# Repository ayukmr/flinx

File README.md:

# flinx

BL654-based low-profile 40% keyboard.

The board uses Kailh Choc V2 switches, and purposely doesn't include any stabilizers.
The PCB fits directly inside the case and is mounted with four screws.
A USB-C port on the side is used for charging, and a switch turns the board on/off.
Once turned on, the keyboard pairs over Bluetooth to send keystrokes.

This is intended as a small board mostly for travel, and as a low-profile version of the Monokei Neko.

## Schematic

## PCB

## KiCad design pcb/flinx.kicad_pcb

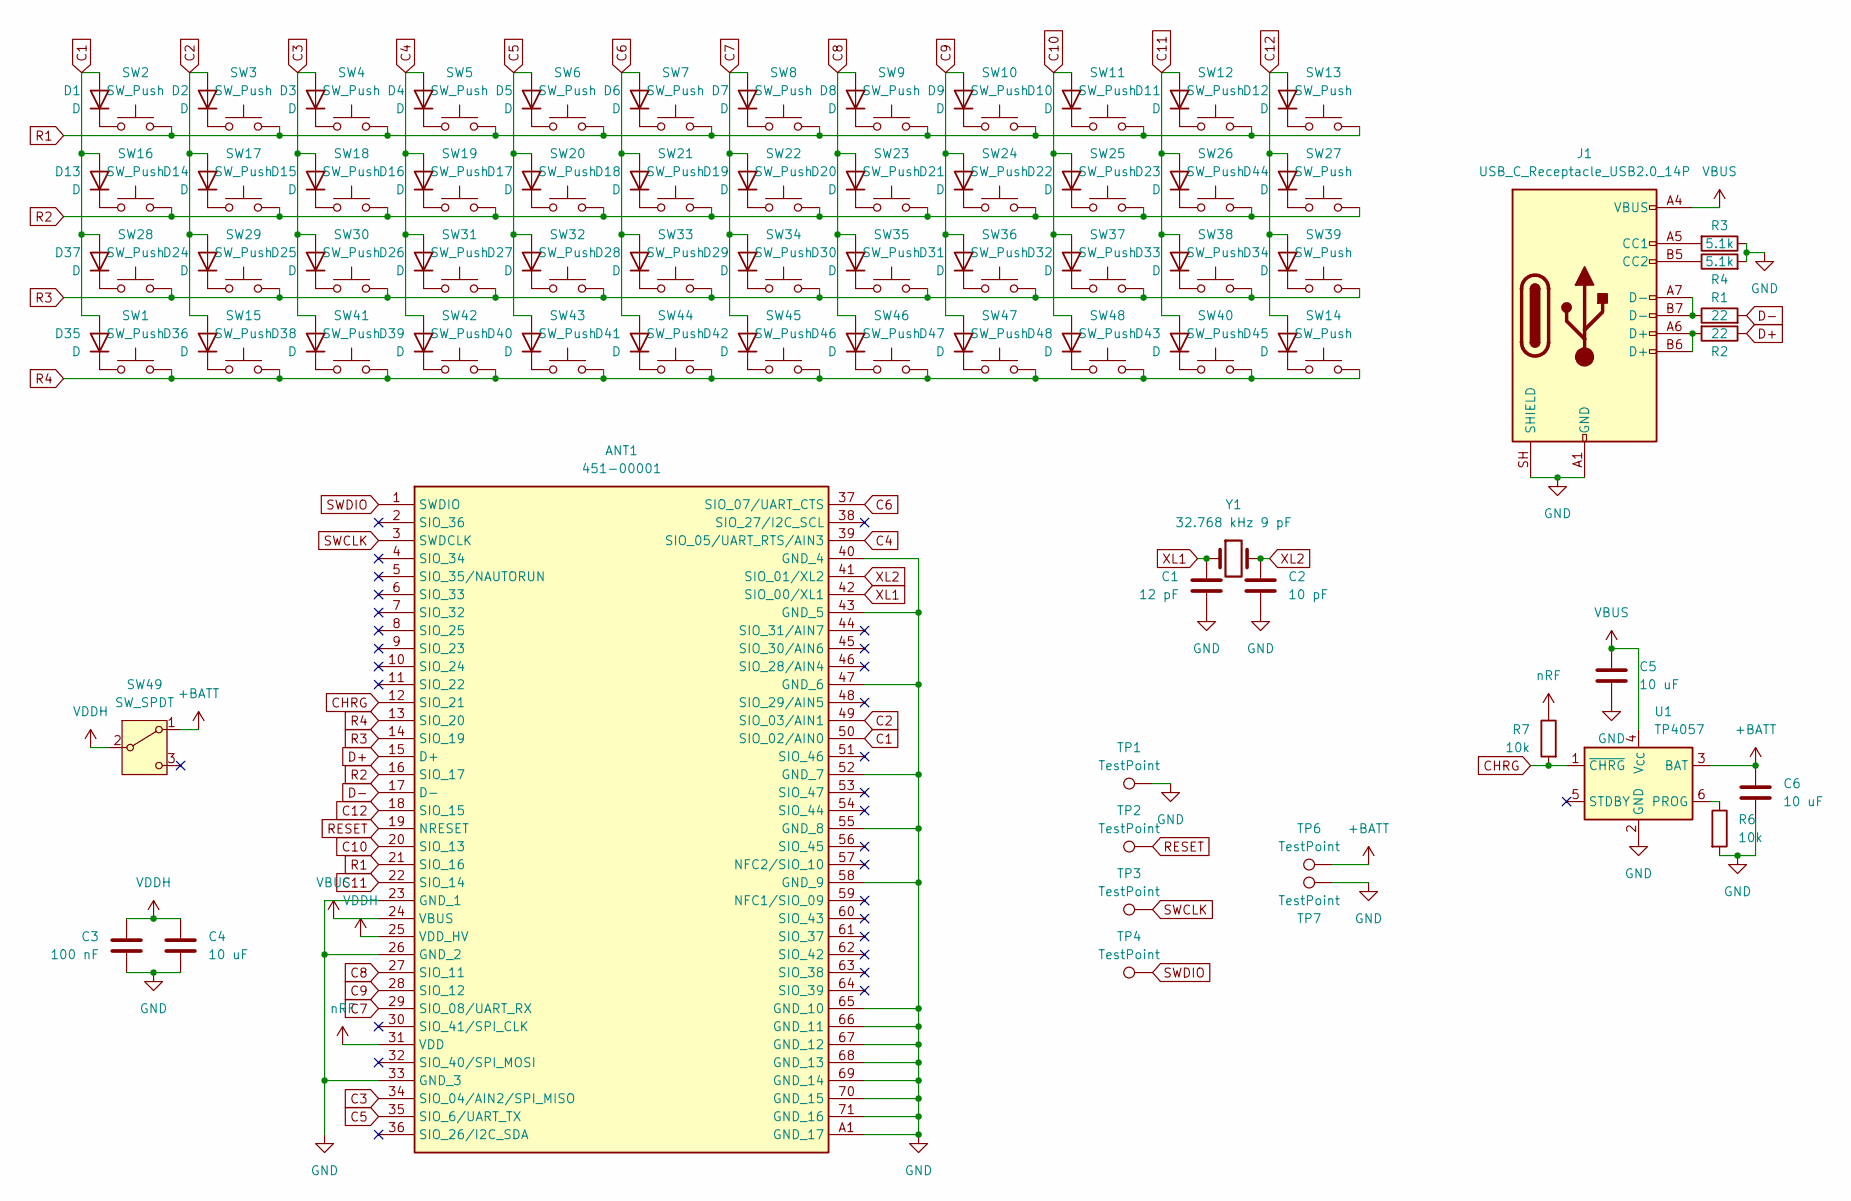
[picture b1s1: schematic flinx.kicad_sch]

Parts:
ANT1: 451-00001; 45100001; Manufacturer_Part_Number 451-00001; Mouser Part Number 814-451-00001
C1: 12 pF; C_0603_1608Metric
C2: 10 pF; C_0603_1608Metric
C3: 100 nF; C_0603_1608Metric
C4, C5, C6: 10 uF; C_0603_1608Metric
D1, D2, D3, D4, D5, D6, D7, D8, D9, D10, D11, D12, D13, D14, D15, D16, D17, D18, D19, D20, D21, D22, D23, D24, D25, D26, D27, D28, D29, D30, D31, D32, D33, D34, D35, D36, D37, D38, D39, D40, D41, D42, D43, D44, D45, D46, D47, D48: D; D_SOD-523
J1: USB_C_Receptacle_USB2.0_14P; USB_C_Receptacle_JAE_DX07S016JA1R1500
R1, R2: 22; R_0603_1608Metric
R3, R4: 5.1k; R_0603_1608Metric
R6, R7: 10k; R_0603_1608Metric
SW1, SW2, SW3, SW4, SW5, SW6, SW7, SW8, SW9, SW10, SW11, SW12, SW13, SW14, SW16, SW17, SW18, SW19, SW20, SW21, SW22, SW23, SW24, SW25, SW26, SW29, SW30, SW31, SW32, SW33, SW34, SW35, SW36, SW37, SW38, SW40, SW41, SW48: SW_Push; SW_Kailh_Choc_V2_1.00u
SW15, SW39, SW42, SW47: SW_Push; SW_Kailh_Choc_V2_1.25u
SW27, SW28, SW43, SW44, SW45, SW46: SW_Push; SW_Kailh_Choc_V2_1.75u
SW49: SW_SPDT; SW_EG1215AA
TP1, TP2, TP3, TP4, TP6, TP7: TestPoint; Pad_SMD_1.5x1.5
U1: TP4057; TSOT-23-6
Y1: 32.768 kHz 9 pF; Crystal_SMD_MicroCrystal_CC7V-T1A-2Pin_3.2x1.5mm_HandSolder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

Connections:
+BATT: C6.2, SW49.1 (A), TP6.1 (1_1), U1.3 (BAT)
C1: ANT1.50 (SIO_02/AIN0), D1.2 (A), D13.2 (A), D35.2 (A), D37.2 (A)
C2: ANT1.49 (SIO_03/AIN1), D2.2 (A), D14.2 (A), D24.2 (A), D36.2 (A)
C3: ANT1.34 (SIO_04/AIN2/SPI_MISO), D3.2 (A), D15.2 (A), D25.2 (A), D38.2 (A)
C4: ANT1.39 (SIO_05/UART_RTS/AIN3), D4.2 (A), D16.2 (A), D26.2 (A), D39.2 (A)
C5: ANT1.35 (SIO_6/UART_TX), D5.2 (A), D17.2 (A), D27.2 (A), D40.2 (A)
C6: ANT1.37 (SIO_07/UART_CTS), D6.2 (A), D18.2 (A), D28.2 (A), D41.2 (A)
C7: ANT1.29 (SIO_08/UART_RX), D7.2 (A), D19.2 (A), D29.2 (A), D42.2 (A)
C8: ANT1.27 (SIO_11), D8.2 (A), D20.2 (A), D30.2 (A), D46.2 (A)
C9: ANT1.28 (SIO_12), D9.2 (A), D21.2 (A), D31.2 (A), D47.2 (A)
C10: ANT1.20 (SIO_13), D10.2 (A), D22.2 (A), D32.2 (A), D48.2 (A)
C11: ANT1.22 (SIO_14), D11.2 (A), D23.2 (A), D33.2 (A), D43.2 (A)
C12: ANT1.18 (SIO_15), D12.2 (A), D34.2 (A), D44.2 (A), D45.2 (A)
CHRG: ANT1.12 (SIO_21), R7.2, U1.1 (~CHRG)
D+: ANT1.15 (D+), R2.1
D-: ANT1.17 (D-), R1.2
GND: ANT1.23 (GND_1), ANT1.26 (GND_2), ANT1.33 (GND_3), ANT1.40 (GND_4), ANT1.43 (GND_5), ANT1.47 (GND_6), ANT1.52 (GND_7), ANT1.55 (GND_8), ANT1.58 (GND_9), ANT1.65 (GND_10), ANT1.66 (GND_11), ANT1.67 (GND_12), ANT1.68 (GND_13), ANT1.69 (GND_14), ANT1.70 (GND_15), ANT1.71 (GND_16), ANT1.A1 (GND_17), C1.2, C2.2, C3.1, C4.1, C5.2, C6.1, J1.A1 (GND), J1.A12 (GND), J1.B1 (GND), J1.B12 (GND), J1.SH (SHIELD), R3.1, R4.2, R6.2, TP1.1 (1_1), TP7.1 (1_1), U1.2 (GND)
unnamed: D1.1 (K), SW2.1
unnamed: D2.1 (K), SW3.1
unnamed: D3.1 (K), SW4.1
unnamed: D4.1 (K), SW5.1
unnamed: D5.1 (K), SW6.1
unnamed: D6.1 (K), SW7.1
unnamed: D7.1 (K), SW8.1
unnamed: D8.1 (K), SW9.1
unnamed: D9.1 (K), SW10.1
unnamed: D10.1 (K), SW11.1
unnamed: D11.1 (K), SW12.1
unnamed: D12.1 (K), SW13.1
unnamed: D13.1 (K), SW16.1
unnamed: D14.1 (K), SW17.1
unnamed: D15.1 (K), SW18.1
unnamed: D16.1 (K), SW19.1
unnamed: D17.1 (K), SW20.1
unnamed: D18.1 (K), SW21.1
unnamed: D19.1 (K), SW22.1
unnamed: D20.1 (K), SW23.1
unnamed: D21.1 (K), SW24.1
unnamed: D22.1 (K), SW25.1
unnamed: D23.1 (K), SW26.1
unnamed: D24.1 (K), SW29.1
unnamed: D25.1 (K), SW30.1
unnamed: D26.1 (K), SW31.1
unnamed: D27.1 (K), SW32.1
unnamed: D28.1 (K), SW33.1
unnamed: D29.1 (K), SW34.1
unnamed: D30.1 (K), SW35.1
unnamed: D31.1 (K), SW36.1
unnamed: D32.1 (K), SW37.1
unnamed: D33.1 (K), SW38.1
unnamed: D34.1 (K), SW39.1
unnamed: D35.1 (K), SW1.1
unnamed: D36.1 (K), SW15.1
unnamed: D37.1 (K), SW28.1
unnamed: D38.1 (K), SW41.1
unnamed: D39.1 (K), SW42.1
unnamed: D40.1 (K), SW43.1
unnamed: D41.1 (K), SW44.1
unnamed: D42.1 (K), SW45.1
unnamed: D43.1 (K), SW40.1
unnamed: D44.1 (K), SW27.1
unnamed: D45.1 (K), SW14.1
unnamed: D46.1 (K), SW46.1
unnamed: D47.1 (K), SW47.1
unnamed: D48.1 (K), SW48.1
unnamed: J1.A5 (CC1), R3.2
unnamed: J1.B5 (CC2), R4.1
unnamed: J1.A6 (D+), J1.B6 (D+), R2.2
unnamed: J1.A7 (D-), J1.B7 (D-), R1.1
unnamed: R6.1, U1.6 (PROG)
R1: ANT1.21 (SIO_16), SW2.2, SW3.2, SW4.2, SW5.2, SW6.2, SW7.2, SW8.2, SW9.2, SW10.2, SW11.2, SW12.2, SW13.2
R2: ANT1.16 (SIO_17), SW16.2, SW17.2, SW18.2, SW19.2, SW20.2, SW21.2, SW22.2, SW23.2, SW24.2, SW25.2, SW26.2, SW27.2
R3: ANT1.14 (SIO_19), SW28.2, SW29.2, SW30.2, SW31.2, SW32.2, SW33.2, SW34.2, SW35.2, SW36.2, SW37.2, SW38.2, SW39.2
R4: ANT1.13 (SIO_20), SW1.2, SW14.2, SW15.2, SW40.2, SW41.2, SW42.2, SW43.2, SW44.2, SW45.2, SW46.2, SW47.2, SW48.2
RESET: ANT1.19 (NRESET), TP2.1 (1_1)
SWCLK: ANT1.3 (SWDCLK), TP3.1 (1_1)
SWDIO: ANT1.1 (SWDIO), TP4.1 (1_1)
VBUS: ANT1.24 (VBUS), C5.1, J1.A4 (VBUS), J1.A9 (VBUS), J1.B4 (VBUS), J1.B9 (VBUS), U1.4 (V_{CC})
VDDH: ANT1.25 (VDD_HV), C3.2, C4.2, SW49.2 (B)
XL1: ANT1.42 (SIO_00/XL1), C1.1, Y1.1
XL2: ANT1.41 (SIO_01/XL2), C2.1, Y1.2
nRF: ANT1.31 (VDD), R7.1

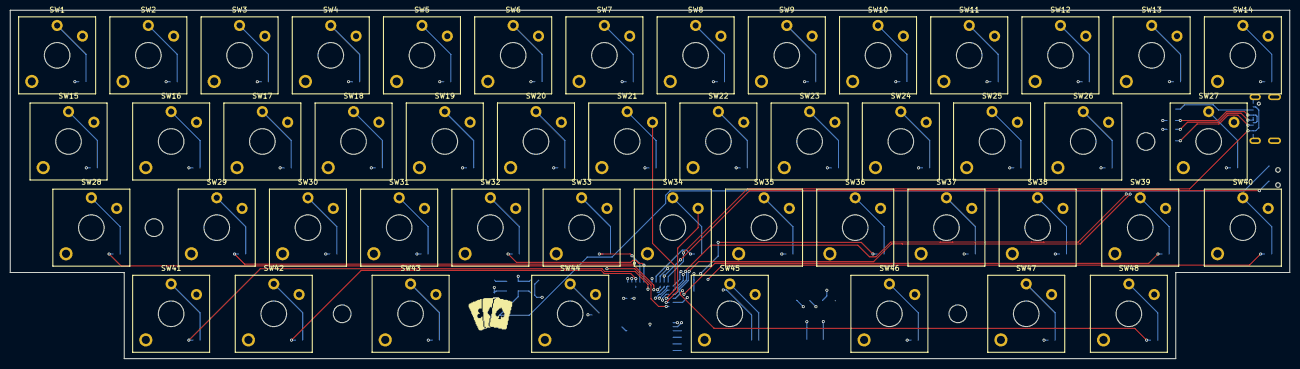
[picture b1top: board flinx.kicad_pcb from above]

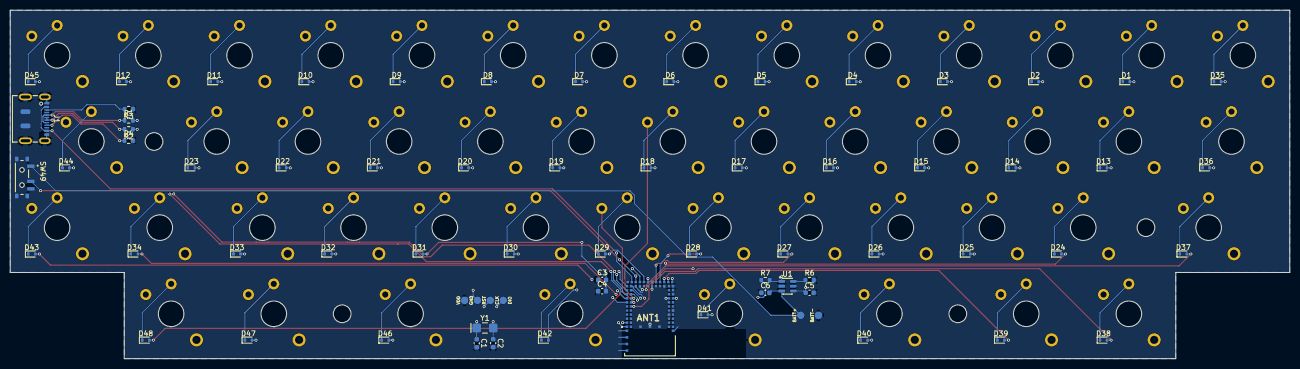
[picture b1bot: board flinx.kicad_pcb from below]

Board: 4 copper layers, 252.5 x 68.8 mm, 119 parts (71 on the bottom side), 82 nets.
